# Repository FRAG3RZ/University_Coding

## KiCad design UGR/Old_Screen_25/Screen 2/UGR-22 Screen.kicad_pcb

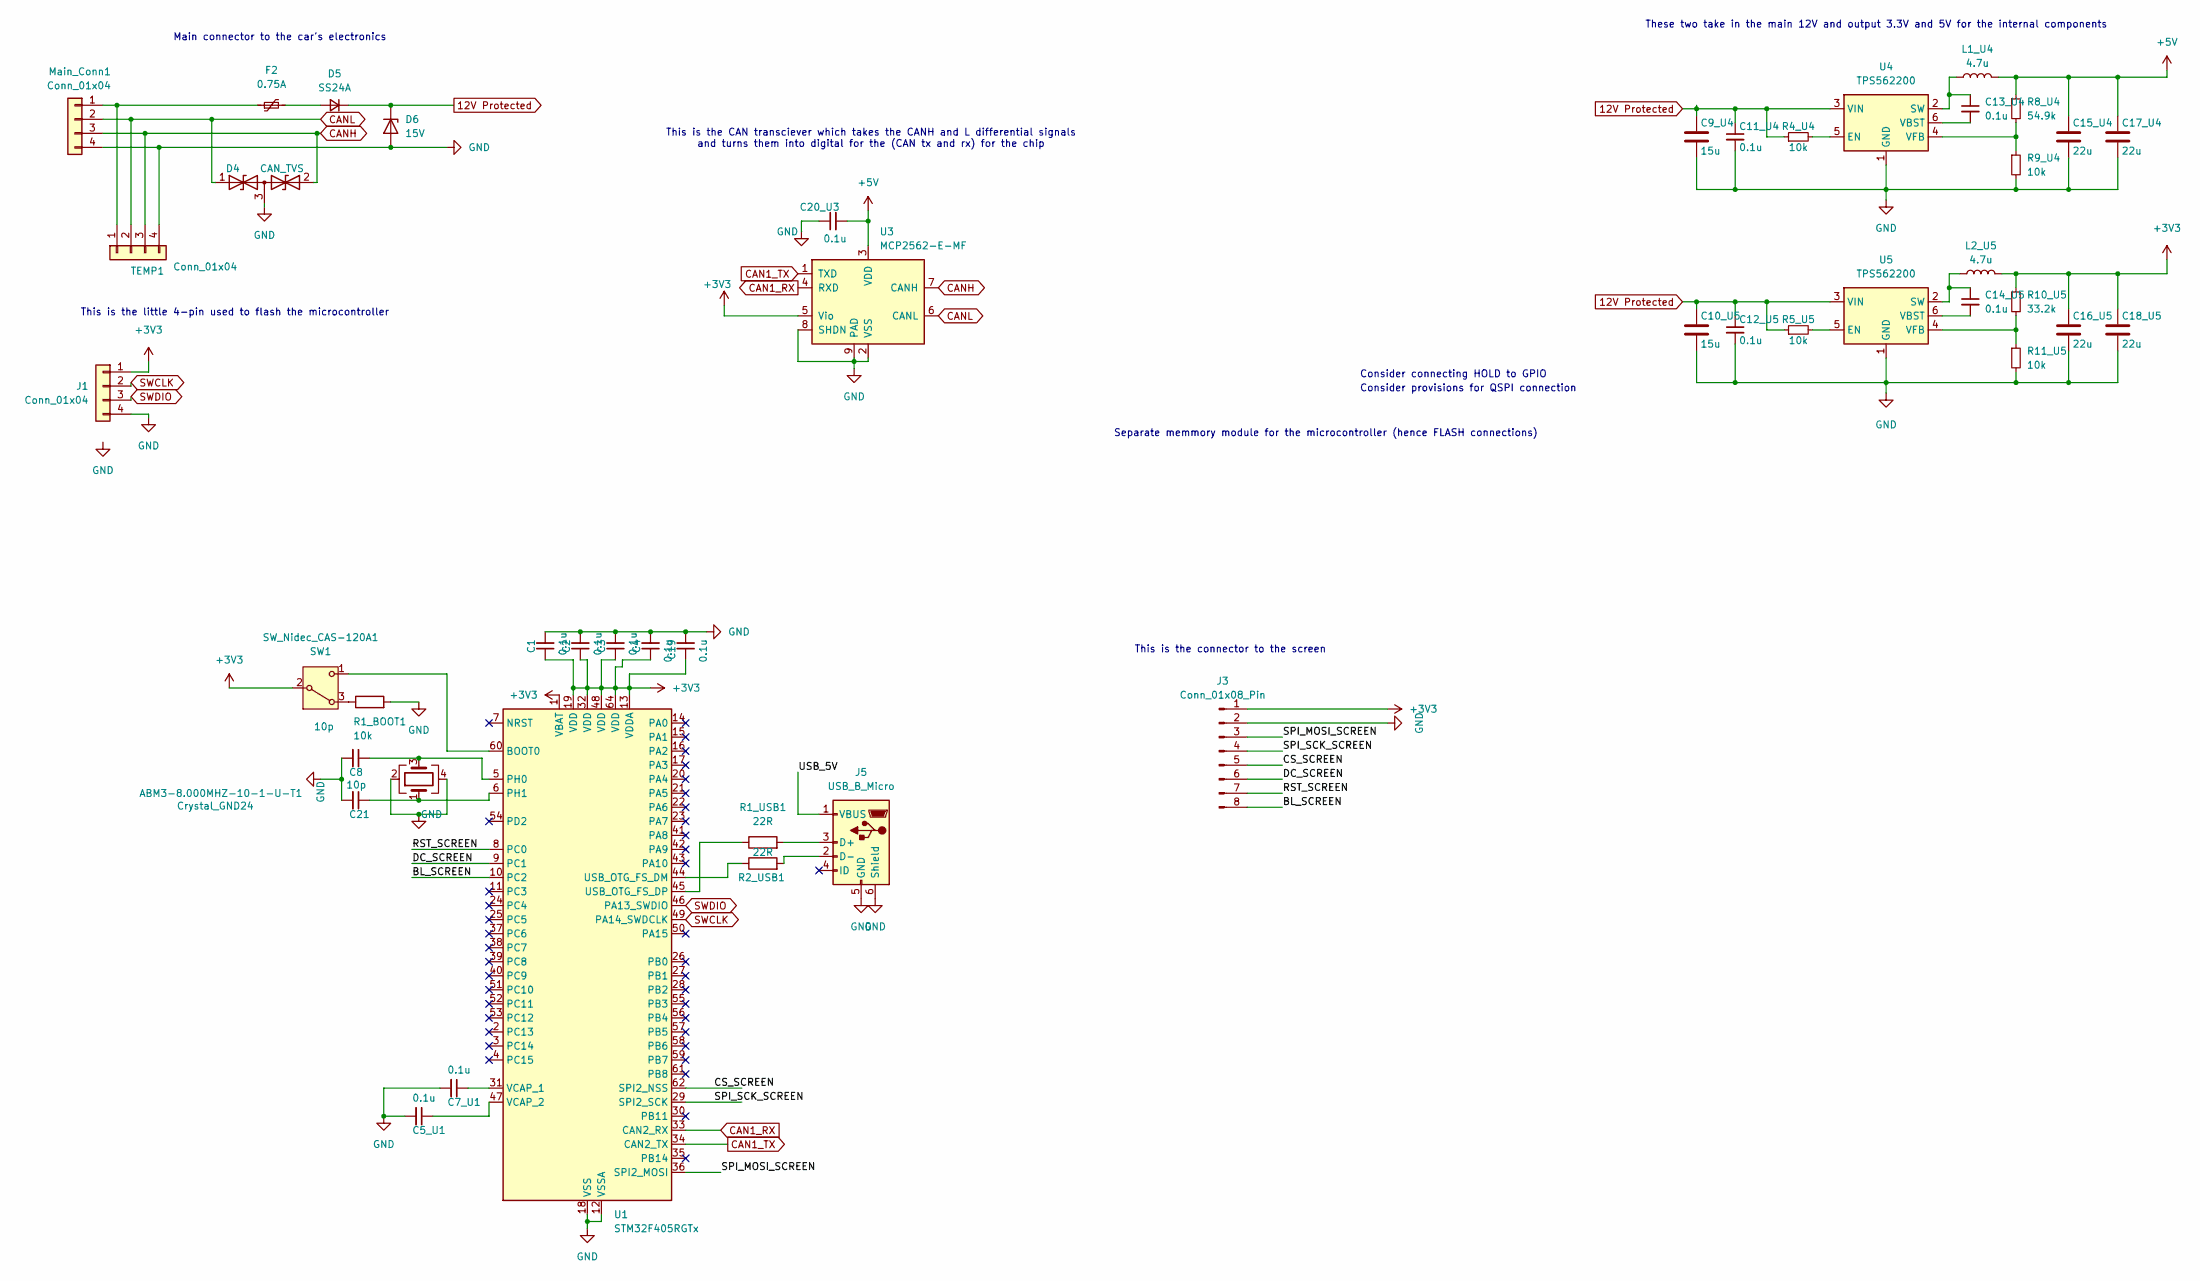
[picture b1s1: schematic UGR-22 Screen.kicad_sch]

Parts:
ABM3-8.000MHZ-10-1-U-T1: Crystal_GND24; Crystal_SMD_Abracon_ABM3B-4Pin_5.0x3.2mm
C1, C2, C3, C4, C5_U1, C7_U1, C11_U4, C12_U5, C13_U4, C14_U5, C19, C20_U3: 0.1u; C_0603_1608Metric_Pad1.08x0.95mm_HandSolder
C8, C21: 10p; C_0603_1608Metric_Pad1.08x0.95mm_HandSolder
C9_U4, C10_U5: 15u; C_1210_3225Metric_Pad1.33x2.70mm_HandSolder
C15_U4, C16_U5, C17_U4, C18_U5: 22u; C_1210_3225Metric_Pad1.33x2.70mm_HandSolder
D4: CAN_TVS; SOT-23; Manufacturer Part No. SZNUP2105L
D5: SS24A; D_SMA; Manufacturer Part No. SS24A
D6: 15V; D_SOD-323_HandSoldering; Manufacturer Part No. SMBJ15A
F2: 0.75A; Fuse_1812_4532Metric_Pad1.30x3.40mm_HandSolder; Manufacturer Part No. 1206L075/16WR
J1: Conn_01x04; PinHeader_1x04_P2.54mm_Vertical
J3: Conn_01x08_Pin; PinHeader_1x08_P2.54mm_Vertical
J5: USB_B_Micro; USB_Micro-B_Wuerth_629105150521
L1_U4, L2_U5: 4.7u; L_0603_1608Metric_Pad1.05x0.95mm_HandSolder
Main_Conn1: Conn_01x04; Bulgin_4_Pin
R1_BOOT1, R4_U4, R5_U5, R9_U4, R11_U5: 10k; R_0603_1608Metric_Pad0.98x0.95mm_HandSolder
R1_USB1, R2_USB1: 22R; R_0603_1608Metric_Pad0.98x0.95mm_HandSolder
R8_U4: 54.9k; R_0603_1608Metric_Pad0.98x0.95mm_HandSolder
R10_U5: 33.2k; R_0603_1608Metric_Pad0.98x0.95mm_HandSolder
SW1: SW_Nidec_CAS-120A1; SW_Slide-03_Wuerth-WS-SLTV_10x2.5x6.4_P2.54mm
TEMP1: Conn_01x04; PinHeader_1x04_P2.54mm_Vertical
U1: STM32F405RGTx; LQFP-64_10x10mm_P0.5mm
U3: MCP2562-E-MF; SOIC-8_3.9x4.9mm_P1.27mm
U4, U5: TPS562200; SOT-23-6

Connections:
12V Protected: C9_U4.1, C10_U5.1, C11_U4.1, C12_U5.1, D5.1 (K), D6.1 (K), R4_U4.1, R5_U5.1, U4.3 (VIN), U5.3 (VIN)
+3V3: C1.1, C2.1, C3.1, C4.1, C16_U5.1, C18_U5.1, C19.1, J1.1, J3.1, L2_U5.2, R10_U5.1, SW1.2 (B), U1.1 (VBAT), U1.13 (VDDA), U1.19 (VDD), U1.32 (VDD), U1.48 (VDD), U1.64 (VDD), U3.5 (Vio); also elsewhere on the board
+5V: C15_U4.1, C17_U4.1, C20_U3.2, L1_U4.2, R8_U4.1, U3.3 (VDD)
/BL_SCREEN: J3.8, U1.10 (PC2)
/CS_SCREEN: J3.5, U1.62 (SPI2_NSS)
/DC_SCREEN: J3.6, U1.9 (PC1)
/RST_SCREEN: J3.7, U1.8 (PC0)
/SPI_MOSI_SCREEN: J3.3, U1.36 (SPI2_MOSI)
/SPI_SCK_SCREEN: J3.4, U1.29 (SPI2_SCK)
/USB_5V: J5.1 (VBUS)
CAN1_RX: U1.33 (CAN2_RX), U3.4 (RXD)
CAN1_TX: U1.34 (CAN2_TX), U3.1 (TXD)
CANH: D4.2 (A2), Main_Conn1.3, TEMP1.3, U3.7 (CANH)
CANL: D4.1 (A1), Main_Conn1.2, TEMP1.2, U3.6 (CANL)
GND: ABM3-8.000MHZ-10-1-U-T1.2, ABM3-8.000MHZ-10-1-U-T1.4, C1.2, C2.2, C3.2, C4.2, C5_U1.2, C7_U1.2, C8.2, C9_U4.2, C10_U5.2, C11_U4.2, C12_U5.2, C15_U4.2, C16_U5.2, C17_U4.2, C18_U5.2, C19.2, C20_U3.1, C21.2, D4.3 (common), D6.2 (A), J1.4, J3.2, J5.5 (GND), J5.6 (Shield), Main_Conn1.4, R1_BOOT1.2, R9_U4.2, R11_U5.2, TEMP1.4, U1.12 (VSSA), U1.18 (VSS), U1.63 (VSS), U3.2 (VSS), U3.8 (SHDN), U3.9 (PAD), U4.1 (GND), U5.1 (GND); also elsewhere on the board
unnamed: D5.2 (A), F2.2
unnamed: J5.3 (D+), R1_USB1.2
unnamed: J5.2 (D-), R2_USB1.2
unnamed: F2.1, Main_Conn1.1, TEMP1.1
unnamed: R1_BOOT1.1, SW1.3 (A)
unnamed: SW1.1 (C), U1.60 (BOOT0)
unnamed: R2_USB1.1, U1.44 (USB_OTG_FS_DM)
unnamed: R1_USB1.1, U1.45 (USB_OTG_FS_DP)
unnamed: ABM3-8.000MHZ-10-1-U-T1.3, C8.1, U1.5 (PH0)
unnamed: ABM3-8.000MHZ-10-1-U-T1.1, C21.1, U1.6 (PH1)
unnamed: C7_U1.1, U1.31 (VCAP_1)
unnamed: C5_U1.1, U1.47 (VCAP_2)
unnamed: R4_U4.2, U4.5 (EN)
unnamed: C13_U4.1, L1_U4.1, U4.2 (SW)
unnamed: C13_U4.2, U4.6 (VBST)
unnamed: R8_U4.2, R9_U4.1, U4.4 (VFB)
unnamed: R5_U5.2, U5.5 (EN)
unnamed: C14_U5.1, L2_U5.1, U5.2 (SW)
unnamed: C14_U5.2, U5.6 (VBST)
unnamed: R10_U5.2, R11_U5.1, U5.4 (VFB)
SWCLK: J1.2, U1.49 (PA14_SWDCLK)
SWDIO: J1.3, U1.46 (PA13_SWDIO)

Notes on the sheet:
These two take in the main 12V and output 3.3V and 5V for the internal components
Consider connecting HOLD to GPIO
This is the connector to the screen
Separate memmory module for the microcontroller (hence FLASH connections)
Consider provisions for QSPI connection
Main connector to the car's electronics
This is the CAN transciever which takes the CANH and L differential signals and turns them into digital for the (CAN tx and rx) for the chip
This is the little 4-pin used to flash the microcontroller

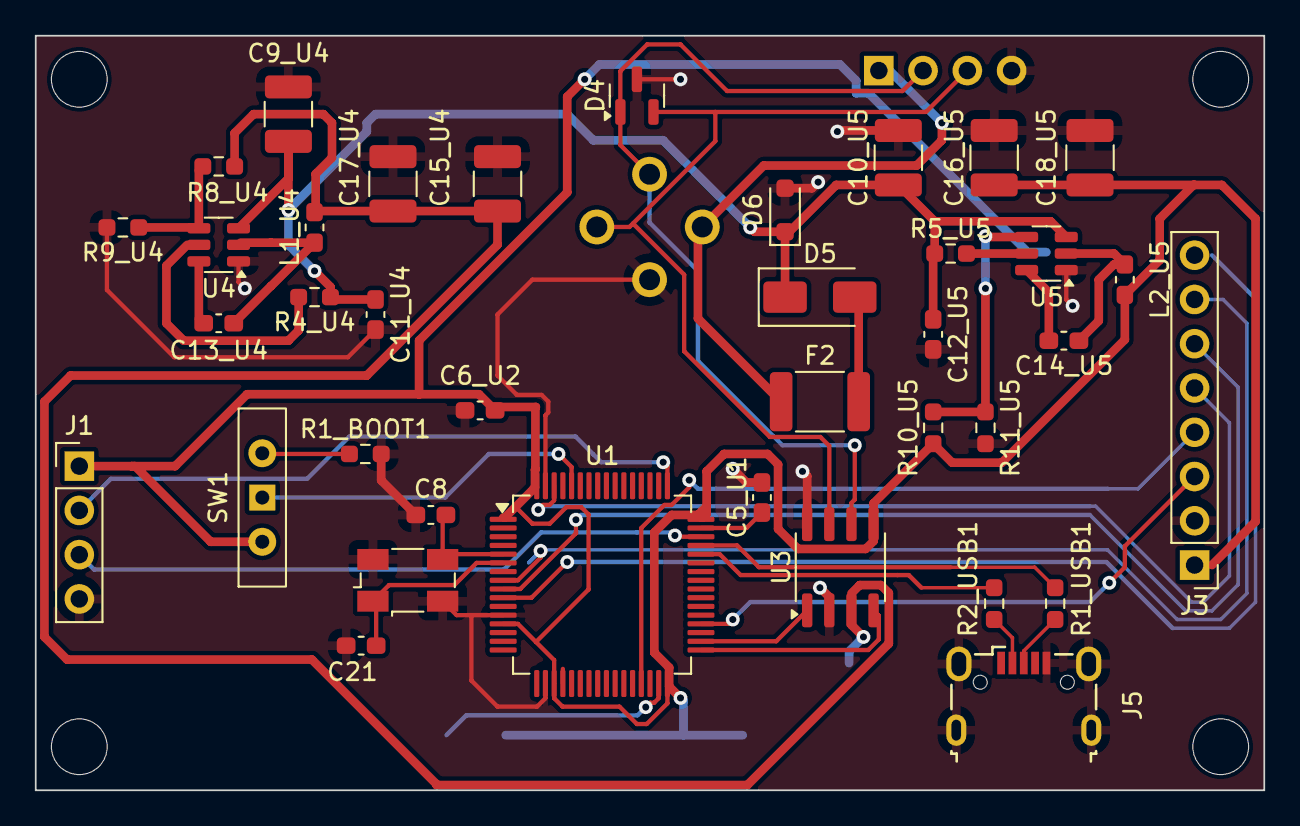
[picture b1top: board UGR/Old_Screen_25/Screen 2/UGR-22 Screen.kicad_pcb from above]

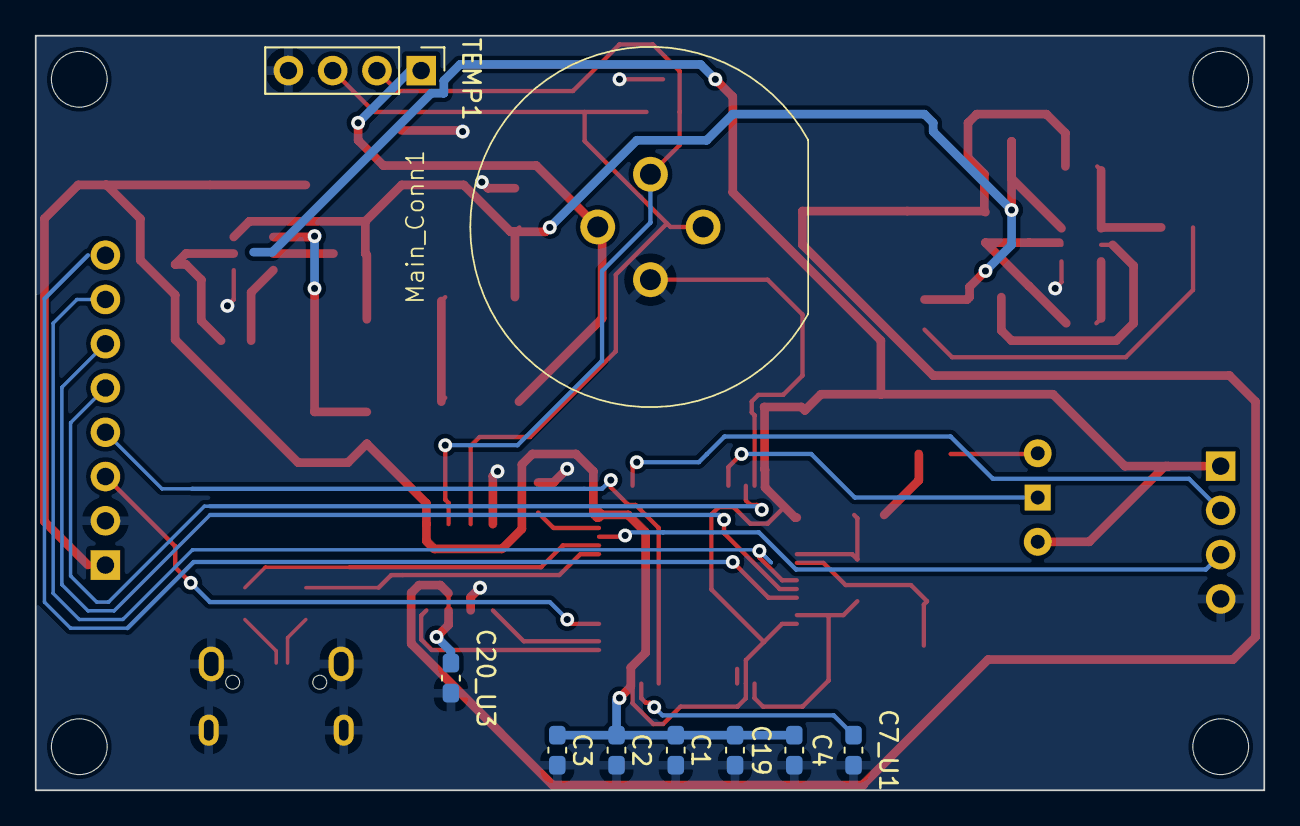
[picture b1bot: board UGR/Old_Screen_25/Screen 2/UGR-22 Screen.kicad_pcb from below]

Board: 2 copper layers, 70.5 x 43.3 mm, 47 parts (9 on the bottom side), 36 nets.

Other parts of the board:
C6_U2: 0.1u; C_0603_1608Metric_Pad1.08x0.95mm_HandSolder

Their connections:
+3V3: C6_U2.2; also elsewhere on the board
GND: C6_U2.1; also elsewhere on the board

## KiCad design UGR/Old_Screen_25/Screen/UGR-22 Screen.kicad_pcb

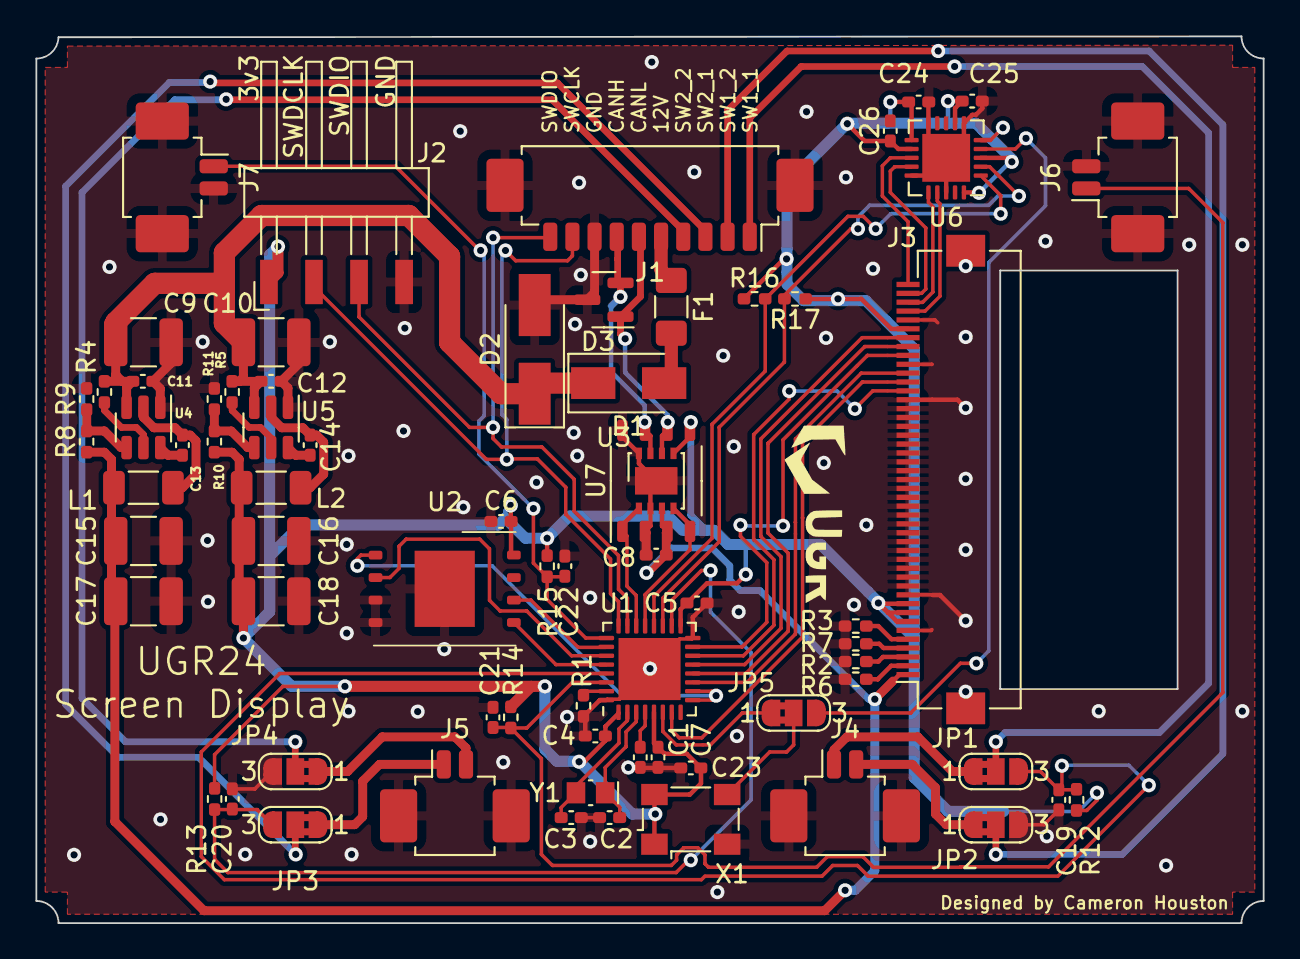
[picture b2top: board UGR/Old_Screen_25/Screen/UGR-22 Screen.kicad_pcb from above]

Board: 2 copper layers, 69.2 x 50.0 mm, 70 parts (0 on the bottom side), 58 nets.

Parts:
C1, C4, C5, C6, C7, C8, C11, C12, C13, C14, C23, C24, C25, C26: 0.1u; C_0402_1005Metric_Pad0.74x0.62mm_HandSolder
C2, C3: 19pF; C_0402_1005Metric_Pad0.74x0.62mm_HandSolder
C9, C10: 15u; C_1210_3225Metric_Pad1.33x2.70mm_HandSolder
C15, C16, C17, C18: 22u; C_1210_3225Metric_Pad1.33x2.70mm_HandSolder
C19, C20, C21, C22: 10n; C_0402_1005Metric_Pad0.74x0.62mm_HandSolder
D1: SS24A; D_SMA
D2: 15V; D_SMA_Handsoldering
D3: CAN_TVS; SOT-23
F1: 0.75A; Fuse_1206_3216Metric_Pad1.42x1.75mm_HandSolder
J1: Conn_01x08_Male; Molex_PicoBlade_53261-1071_1x10-1MP_P1.25mm_Horizontal
J2: SWD; Harwin_M20-89004xx_1x04_P2.54mm_Horizontal
J3: DT028ATFT; Hirose_FH12-45S-0.5SH_1x45-1MP_P0.50mm_Horizontal
J4: SW1; Molex_PicoBlade_53261-0271_1x02-1MP_P1.25mm_Horizontal
J5: SW2; Molex_PicoBlade_53261-0271_1x02-1MP_P1.25mm_Horizontal
J6: SW3; Molex_PicoBlade_53261-0271_1x02-1MP_P1.25mm_Horizontal
J7: SW4; Molex_PicoBlade_53261-0271_1x02-1MP_P1.25mm_Horizontal
JP1, JP3, JP5: JMP_SW1_1; SolderJumper-3_P1.3mm_Bridged2Bar12_RoundedPad1.0x1.5mm_Num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
JP2, JP4: JMP_SW1_2; SolderJumper-3_P1.3mm_Bridged2Bar12_RoundedPad1.0x1.5mm_Num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
L1, L2: 4.7u; L_1206_3216Metric_Pad1.22x1.90mm_HandSolder
R1, R4, R5, R9, R11: 10k; R_0402_1005Metric_Pad0.72x0.64mm_HandSolder
R2, R3, R6, R7: 100; R_0402_1005Metric_Pad0.72x0.64mm_HandSolder
R8: 56.2k; R_0402_1005Metric_Pad0.72x0.64mm_HandSolder
R10: 29.4k; R_0402_1005Metric_Pad0.72x0.64mm_HandSolder
R12, R13, R14, R15: 1K; R_0402_1005Metric_Pad0.72x0.64mm_HandSolder
R16, R17: 1.2k; R_0402_1005Metric_Pad0.72x0.64mm_HandSolder
U1: STM32L432K; UFQFPN-32-1EP_5x5mm_P0.5mm_EP3.5x3.5mm
U2: S25FL128S; WSON-8-1EP_8x6mm_P1.27mm_EP3.4x4.3mm
U3: MCP2562-E-MF; DFN-8-1EP_3x3mm_P0.65mm_EP1.55x2.4mm
U4, U5: TPS562200; SOT-23-6
U6: TSC2004IRTJ; QFN-20-1EP_4x4mm_P0.5mm_EP2.7x2.7mm
U7: MCP2562-E-SN; SOIC-8_3.9x4.9mm_P1.27mm
X1: 8MHz; Oscillator_SMD_Fordahl_DFAS15-4Pin_5.0x3.2mm
Y1: 32.768KHz; Crystal_SMD_MicroCrystal_CM9V-T1A-2Pin_1.6x1.0mm_HandSolder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

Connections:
12V Protected: C9.1, C10.1, C11.1, C12.1, D1.1 (K), D2.1 (K), R4.1, R5.1, U4.3 (VIN), U5.3 (VIN)
+3V3: C4.1, C5.1, C6.2, C7.1, C16.1, C18.1, C23.1, C24.1, C25.1, C26.1, J2.1, J3.7 (IM1), J3.8 (IM2), J3.9 (IM3), J3.40 (VCC), L2.2, R10.1, R12.2, R13.2, R14.2, R15.2, R16.1, R17.1, U1.1 (VDD), U1.5 (VDDA/VREF+), U1.17 (VDD), U2.8 (VCC), U3.5 (Vio), U6.3 (AD1), U6.5 (~RESET), U6.7 (I/OVDD), U6.11 (VREF), U6.12 (SNSVDD), U6.20 (AD0), U7.5 (Vio), X1.1 (Vctrl), X1.4 (V+)
+5V: C8.2, C15.1, C17.1, J3.1 (LED_A), L1.2, R8.1, U3.3 (VDD), U7.3 (VDD)
CAN1_RX: U1.21 (PA11), U3.4 (RXD), U7.4 (RXD)
CAN1_TX: U1.22 (PA12), U3.1 (TXD), U7.1 (TXD)
CANH: D3.2 (A2), J1.7, U3.7 (CANH), U7.7 (CANH)
CANL: D3.1 (A1), J1.6, U3.6 (CANL), U7.6 (CANL)
FLASH_CS: U1.9 (PA3), U1.10 (PA4), U2.1 (CS#)
FLASH_MISO: U1.27 (PB4), U2.2 (SO/IO1)
FLASH_MOSI: U1.28 (PB5), U2.5 (SI/IO0)
FLASH_SCK: U1.26 (PB3), U2.6 (SCK)
GND: C1.2, C2.2, C3.2, C4.2, C5.2, C6.1, C7.2, C8.1, C9.2, C10.2, C11.2, C12.2, C15.2, C16.2, C17.2, C18.2, C19.2, C20.2, C21.2, C22.2, C23.2, C24.2, C25.2, C26.2, D2.2 (A), D3.3 (common), J1.8, J1.MP (MountPin), J2.4, J3.6 (IM0), J3.10 (FMARK), J3.11 (VSYNC), J3.12 (HSYNC), J3.13 (DOTCLK), J3.14 (ENABLE), J3.15 (DB17), J3.16 (DB16), J3.17 (DB15), J3.18 (DB14), J3.19 (DB13), J3.20 (DB12), J3.21 (DB11), J3.22 (DB10), J3.23 (DB9), J3.24 (DB8), J3.25 (DB7), J3.26 (DB6), J3.27 (DB5), J3.28 (DB4), J3.29 (DB3), J3.30 (DB2), J3.31 (DB1), J3.32 (DB0), J3.36 (RD), J3.41 (GND), J4.MP (MountPin), J5.MP (MountPin), J6.2, J6.MP (MountPin), J7.2, J7.MP (MountPin), JP2.3 (B), JP4.3 (B), R1.1, R2.1, R3.1, R6.2, R7.2, R9.2, R11.2, U1.16 (VSS), U1.32 (VSS), U1.33 (PAD), U2.3 (WP#/IO2), U2.4 (VSS), U2.9 (PAD), U3.2 (VSS), U3.8 (SHDN), U3.9 (PAD), U4.1 (GND), U5.1 (GND), U6.6 (DGND), U6.10 (AGND), U6.15 (SUBGND), U6.18 (SNSGND), U6.21 (PAD), U7.2 (VSS), U7.8 (STBY), X1.2 (GND)
I2C1_SCL: R17.2, U1.19 (PA9), U6.2 (SCL)
I2C1_SDA: R16.2, U1.20 (PA10), U6.1 (SDA)
LCD_CS: J3.33 (CS), U1.14 (PB0)
LCD_DC: J3.34 (WR), U1.7 (PA1)
LCD_MISO: J3.38 (SDO), U1.12 (PA6)
LCD_MOSI: J3.39 (SDI), U1.13 (PA7)
LCD_RST: J3.37 (RESET), U1.15 (PB1)
LCD_SCL: J3.35 (RS/SCL), U1.11 (PA5)
LCD_XL: J3.45 (NC/XL), U6.13 (X+)
LCD_XR: J3.43 (NC/XR), U6.16 (X-)
LCD_YD: J3.42 (NC/TD), U6.17 (Y-)
LCD_YU: J3.44 (NC/YU), U6.14 (Y+)
MCU_RX: C22.1, J7.1, R15.1, U1.25 (PA15)
unnamed: C1.1, U1.4 (NRST)
unnamed: C2.1, U1.3 (PC15-OSC32_OUT), Y1.1
unnamed: C3.1, U1.2 (PC14-OSC32_IN), Y1.2
unnamed: C13.1, L1.1, U4.2 (SW)
unnamed: C13.2, U4.6 (VBST)
unnamed: C14.1, L2.1, U5.2 (SW)
unnamed: C14.2, U5.6 (VBST)
unnamed: D1.2 (A), F1.2
unnamed: F1.1, J1.5
unnamed: J3.2 (LED_K1), R6.1
unnamed: J3.3 (LED_K2), R2.2
unnamed: J3.4 (LED_K3), R7.1
unnamed: J3.5 (LED_K4), R3.2
unnamed: J4.1, JP1.1 (A)
unnamed: J4.2, JP2.1 (A)
unnamed: J5.1, JP3.1 (A)
unnamed: J5.2, JP4.1 (A)
unnamed: JP5.1 (A), U1.6 (PA0/CK_IN)
unnamed: JP5.2 (C), X1.3 (OUT)
unnamed: R1.2, U1.31 (PH3/BOOT0)
unnamed: R4.2, U4.5 (EN)
unnamed: R5.2, U5.5 (EN)
unnamed: R8.2, R9.1, U4.4 (VFB)
unnamed: R10.2, R11.1, U5.4 (VFB)
SW1_1: J1.1, JP1.2 (C)
SW1_2: J1.2, JP2.2 (C)
SW2_2: J1.3, J1.4, JP4.2 (C)
SWCLK: J1.9, J2.2, U1.24 (PA14)
SWDIO: J1.10, J2.3, U1.23 (PA13)
SWITCH_1: C19.1, JP1.3 (B), R12.1, U1.29 (PB6)
SWITCH_2: C20.1, JP3.3 (B), R13.1, U1.18 (PA8)
SWITCH_3: C21.1, J6.1, R14.1, U1.30 (PB7)
TS_IRQ: JP5.3 (B), U6.4 (~PINTDAV)

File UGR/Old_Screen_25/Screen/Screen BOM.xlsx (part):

Ref | Val | Footprint | Datasheet |  | LCSC | Part no | NOTES | order codes
C1 | 0.1u | Capacitor_SMD:C_0402_1005Metric_Pad0.74x0.62mm_HandSolder | ~ | book | Mouser |  | https://www.mouser.co.uk/ProductDetail/KEMET/C0402C104M4RACT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
C2 | 19pF | Capacitor_SMD:C_0402_1005Metric_Pad0.74x0.62mm_HandSolder | ~ | no | Mouser |  | https://www.mouser.co.uk/ProductDetail/Murata-Electronics/GJ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
C3 | 19pF | Capacitor_SMD:C_0402_1005Metric_Pad0.74x0.62mm_HandSolder | ~ | no | Mouser
C4 | 0.1u | Capacitor_SMD:C_0402_1005Metric_Pad0.74x0.62mm_HandSolder | ~ | no | Mouser
C5 | 0.1u | Capacitor_SMD:C_0402_1005Metric_Pad0.74x0.62mm_HandSolder | ~ | no | Mouser
C6 | 0.1u | Capacitor_SMD:C_0402_1005Metric_Pad0.74x0.62mm_HandSolder | ~ | no | Mouser
C7 | 0.1u | Capacitor_SMD:C_0402_1005Metric_Pad0.74x0.62mm_HandSolder | ~ | no | Mouser
C8 | 0.1u | Capacitor_SMD:C_0402_1005Metric_Pad0.74x0.62mm_HandSolder | ~ | no | Mouser
C9 | 15u | Capacitor_SMD:C_1210_3225Metric_Pad1.33x2.70mm_HandSolder | ~ | no | Mouser |  | https://www.mouser.co.uk/ProductDetail/KEMET/C1210C156K4PACT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
C10 | 15u | Capacitor_SMD:C_1210_3225Metric_Pad1.33x2.70mm_HandSolder | ~ | no | Mouser
C11 | 0.1u | Capacitor_SMD:C_0402_1005Metric_Pad0.74x0.62mm_HandSolder | ~ | no | Mouser
C12 | 0.1u | Capacitor_SMD:C_0402_1005Metric_Pad0.74x0.62mm_HandSolder | ~ | no | Mouser
C13 | 0.1u | Capacitor_SMD:C_0402_1005Metric_Pad0.74x0.62mm_HandSolder | ~ | no | Mouser
C14 | 0.1u | Capacitor_SMD:C_0402_1005Metric_Pad0.74x0.62mm_HandSolder | ~ | no | Mouser
C15 | 22u | Capacitor_SMD:C_1210_3225Metric_Pad1.33x2.70mm_HandSolder | ~ | no | Mouser |  | https://www.mouser.co.uk/ProductDetail/KEMET/C1210C226K8RACT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
C16 | 22u | Capacitor_SMD:C_1210_3225Metric_Pad1.33x2.70mm_HandSolder | ~ | no | Mouser
C17 | 22u | Capacitor_SMD:C_1210_3225Metric_Pad1.33x2.70mm_HandSolder | ~ | no | Mouser
C18 | 22u | Capacitor_SMD:C_1210_3225Metric_Pad1.33x2.70mm_HandSolder | ~ | no | Mouser
C19 | 10n | Capacitor_SMD:C_0402_1005Metric_Pad0.74x0.62mm_HandSolder | ~ | book | 8 + more in book
C20 | 10n | Capacitor_SMD:C_0402_1005Metric_Pad0.74x0.62mm_HandSolder | ~ | book
C21 | 10n | Capacitor_SMD:C_0402_1005Metric_Pad0.74x0.62mm_HandSolder | ~ | book
C22 | 10n | Capacitor_SMD:C_0402_1005Metric_Pad0.74x0.62mm_HandSolder | ~ | book
C23 | 0.1u | Capacitor_SMD:C_0402_1005Metric_Pad0.74x0.62mm_HandSolder | ~ | no | Mouser
C24 | 0.1u | Capacitor_SMD:C_0402_1005Metric_Pad0.74x0.62mm_HandSolder | ~ | no | Mouser
C25 | 0.1u | Capacitor_SMD:C_0402_1005Metric_Pad0.74x0.62mm_HandSolder | ~ | no | Mouser
C26 | 0.1u | Capacitor_SMD:C_0402_1005Metric_Pad0.74x0.62mm_HandSolder | ~ | no | Mouser
D1 | SS24A | Diode_SMD:D_SMA | https://docs.rs-online.com/a7bf/0900766b814bbf7a.pdf | book | 5 | SS24A | Should be in book! | RS 917-9186
D2 | 15V | Diode_SMD:D_SMA_Handsoldering | https://docs.rs-online.com/5c35/0900766b813439e9.pdf | yes | 4 | SMBJ15A | Should be in book! | Farnell 2675420
D3 | CAN_TVS | Package_TO_SOT_SMD:SOT-23 | https://www.onsemi.com/pdf/datasheet/nup2105l-d.pdf |  | CDSOT23-T24CAN | SZNUP2105L | ALT: CDSOT23-T24CAN , uClamp2492SQ | Farnell 2533287 | https://www.mouser.co.uk/ProductDetail/Bourns/CDSOT23-T24CAN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
F1 | 0.75A | Fuse:Fuse_1206_3216Metric_Pad1.42x1.75mm_HandSolder | ~ |  | 5 | 1206L075/16WR | Should be in book! | Farnell 2786572
J1 | Conn_01x10_Male | Connector_Molex:Molex_PicoBlade_53261-1071_1x10-1MP_P1.25mm_Horizontal | ~ |  | Mouser | 53261-1071 |  | RS 542-7179 | https://www.mouser.co.uk/ProductDetail/Molex/53261-1071?qs=%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
J2 | SWD | Connector_Harwin:Harwin_M20-89004xx_1x04_P2.54mm_Horizontal | ~
J3 | DT028ATFT | Connector_FFC-FPC:Hirose_FH12-45S-0.5SH_1x45-1MP_P0.50mm_Horizontal | https://www.mouser.co.uk/datasheet/2/1015/DT028ATFT-v21-1650620.pdf |  | Mouser |  | Should be in book! and we have a spare screen! | RS 772-7027 | https://www.mouser.co.uk/ProductDetail/Hirose-Connector/FH12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
J4 | SW1 | Connector_Molex:Molex_PicoBlade_53261-0271_1x02-1MP_P1.25mm_Horizontal | ~ |  | Mouser |  |  | RS 542-7090 | https://www.mouser.co.uk/ProductDetail/Molex/53261-0271?qs=%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
J5 | SW2 | Connector_Molex:Molex_PicoBlade_53261-0271_1x02-1MP_P1.25mm_Horizontal | ~ |  | Mouser |  |  | RS 542-7090
J6 | SW3 | Connector_Molex:Molex_PicoBlade_53261-0271_1x02-1MP_P1.25mm_Horizontal | ~ |  | Mouser |  |  | RS 542-7090
J7 | SW4 | Connector_Molex:Molex_PicoBlade_53261-0271_1x02-1MP_P1.25mm_Horizontal | ~ |  | Mouser |  |  | RS 542-7090
JP1 | JMP_SW1_1 | Jumper:SolderJumper-3_P1.3mm_Bridged2Bar12_RoundedPad1.0x1.5mm_NumberLabels | ~
JP2 | JMP_SW1_2 | Jumper:SolderJumper-3_P1.3mm_Bridged2Bar12_RoundedPad1.0x1.5mm_NumberLabels | ~
JP3 | JMP_SW1_1 | Jumper:SolderJumper-3_P1.3mm_Bridged2Bar12_RoundedPad1.0x1.5mm_NumberLabels | ~
JP4 | JMP_SW1_2 | Jumper:SolderJumper-3_P1.3mm_Bridged2Bar12_RoundedPad1.0x1.5mm_NumberLabels | ~
JP5 | JMP_SW1_1 | Jumper:SolderJumper-3_P1.3mm_Bridged2Bar12_RoundedPad1.0x1.5mm_NumberLabels | ~
L1 | 4.7u | Inductor_SMD:L_1206_3216Metric_Pad1.22x1.90mm_HandSolder | ~ |  | Mouser |  | Should be in book but check! specifically 1206 4.7u inductors | 786-7188 | https://www.mouser.co.uk/ProductDetail/Murata-Electronics/LQ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
L2 | 4.7u | Inductor_SMD:L_1206_3216Metric_Pad1.22x1.90mm_HandSolder | ~ |  | Mouser |  | Should be in book but check! specifically 1206 4.7u inductors
R1 | 10k | Resistor_SMD:R_0402_1005Metric_Pad0.72x0.64mm_HandSolder | ~
R2 | 100 | Resistor_SMD:R_0402_1005Metric_Pad0.72x0.64mm_HandSolder | ~
R3 | 100 | Resistor_SMD:R_0402_1005Metric_Pad0.72x0.64mm_HandSolder | ~
R4 | 10k | Resistor_SMD:R_0402_1005Metric_Pad0.72x0.64mm_HandSolder | ~
R5 | 10k | Resistor_SMD:R_0402_1005Metric_Pad0.72x0.64mm_HandSolder | ~
R6 | 100 | Resistor_SMD:R_0402_1005Metric_Pad0.72x0.64mm_HandSolder | ~
R7 | 100 | Resistor_SMD:R_0402_1005Metric_Pad0.72x0.64mm_HandSolder | ~
R8 | 56.2k | Resistor_SMD:R_0402_1005Metric_Pad0.72x0.64mm_HandSolder | ~ |  | find
R9 | 10k | Resistor_SMD:R_0402_1005Metric_Pad0.72x0.64mm_HandSolder | ~
R10 | 29.4k | Resistor_SMD:R_0402_1005Metric_Pad0.72x0.64mm_HandSolder | ~ |  | find
R11 | 10k | Resistor_SMD:R_0402_1005Metric_Pad0.72x0.64mm_HandSolder | ~
R12 | 1K | Resistor_SMD:R_0402_1005Metric_Pad0.72x0.64mm_HandSolder | ~
R13 | 1K | Resistor_SMD:R_0402_1005Metric_Pad0.72x0.64mm_HandSolder | ~
R14 | 1K | Resistor_SMD:R_0402_1005Metric_Pad0.72x0.64mm_HandSolder | ~
R15 | 1K | Resistor_SMD:R_0402_1005Metric_Pad0.72x0.64mm_HandSolder | ~
R16 | 1.2k | Resistor_SMD:R_0402_1005Metric_Pad0.72x0.64mm_HandSolder | ~
R17 | 1.2k | Resistor_SMD:R_0402_1005Metric_Pad0.72x0.64mm_HandSolder | ~
U1 | STM32L432K | Package_DFN_QFN:UFQFPN-32-1EP_5x5mm_P0.5mm_EP3.5x3.5mm |  |  | C94784 | STM32L432KCU6 | will be difficult to find! can also try STM32L432KB, as long as its 32 pin QFN | RS 196-2081 | WHICH
U2 | S25FL128S | Library:WSON-8-1EP_8x6mm_P1.27mm_EP3.4x4.3mm |  |  |  |  | dont worry about this
U3 | MCP2562-E-MF | Package_DFN_QFN:DFN-8-1EP_3x3mm_P0.65mm_EP1.55x2.4mm | http://ww1.microchip.com/downloads/en/DeviceDoc/25167A.pdf |  |  |  | out of stock on RS, may need new PCB with larger footprint! small job | RS 824-6434
U4 | TPS562200 | Package_TO_SOT_SMD:SOT-23-6 | http://www.ti.com/lit/ds/symlink/tps563200.pdf |  | 62208 versiom |  | Should be in book! note that theres 62201 and 62208 and whatever but they all w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
U5 | TPS562200 | Package_TO_SOT_SMD:SOT-23-6 | http://www.ti.com/lit/ds/symlink/tps563200.pdf |  | ^ |  | Should be in book! | RS 133-0751
U6 | TSC2004IRTJ | Package_DFN_QFN:QFN-20-1EP_4x4mm_P0.5mm_EP2.7x2.7mm |  |  |  |  | dont worry about this, its an optional touch screen controller
X1 | 8MHz | Oscillator:Oscillator_SMD_Fordahl_DFAS15-4Pin_5.0x3.2mm | https://docs.rs-online.com/b87a/0900766b81674608.pdf |  | maybe?? | 636L3I024M00000 | is it 8 or 24?? | RS 178-2583
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
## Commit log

2025-10-15 Project Changes
2025-10-31 Comms 3 + Rover
2025-11-05 new main
2025-11-05 added a break function
